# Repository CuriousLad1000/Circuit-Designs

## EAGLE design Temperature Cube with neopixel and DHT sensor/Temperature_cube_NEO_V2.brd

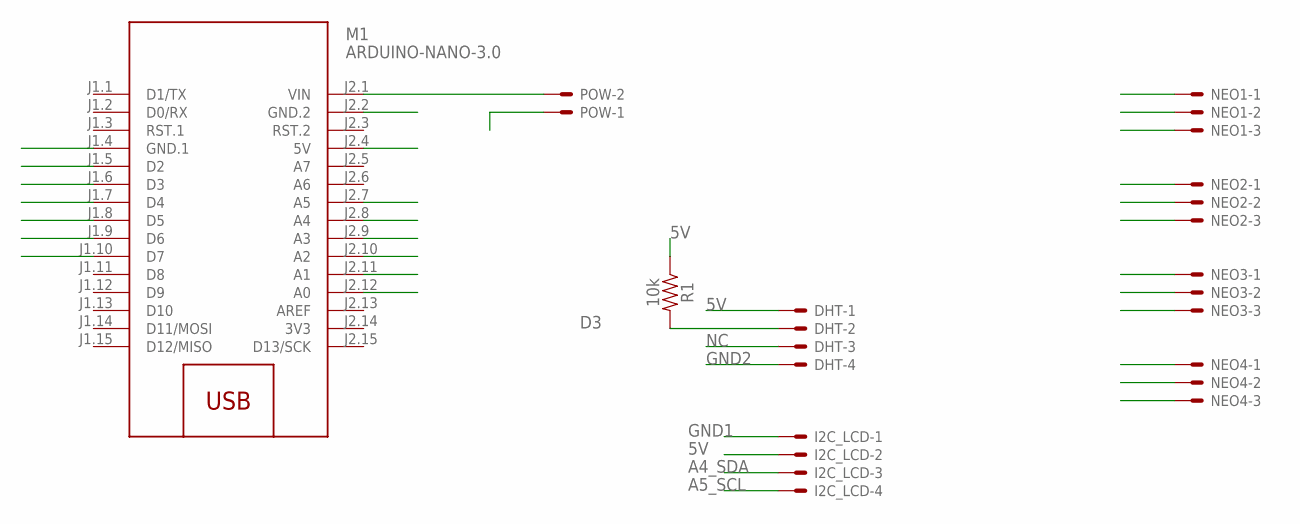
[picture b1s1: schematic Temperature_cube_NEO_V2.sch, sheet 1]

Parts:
DHT: JST-XH-04-PIN-ROUND-PAD; JST-XH-04-PACKAGE-ROUND-PAD
I2C_LCD: JST-XH-04-PIN-ROUND-PAD; JST-XH-04-PACKAGE-ROUND-PAD
M1: ARDUINO-NANO-3.0
NEO1, NEO2, NEO3, NEO4: JST-XH-03-PIN-ROUND-PAD; JST-XH-03-PACKAGE-ROUND-PAD
POW: JST-XH-02-PIN-ROUND-PAD; JST-XH-02-PACKAGE-ROUND-PAD
R1: 10k; AXIAL-0.3

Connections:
3V3: M1.J2.14 (3V3)
5V: DHT.1, I2C_LCD.2, M1.J2.4 (5V), NEO1.1, NEO2.1, NEO3.1, NEO4.1, R1.P$1 (1)
A0: M1.J2.12 (A0), NEO1.2
A1: M1.J2.11 (A1), NEO2.2
A2: M1.J2.10 (A2), NEO3.2
A3: M1.J2.9 (A3), NEO4.2
A4_SDA: I2C_LCD.3, M1.J2.8 (A4)
A5_SCL: I2C_LCD.4, M1.J2.7 (A5)
D2: M1.J1.5 (D2)
D3: DHT.2, M1.J1.6 (D3), R1.P$2 (2)
D4: M1.J1.7 (D4)
D5: M1.J1.8 (D5)
D6: M1.J1.9 (D6)
D7: M1.J1.10 (D7)
GND1: I2C_LCD.1, M1.J1.4 (GND.1), NEO3.3, NEO4.3
GND2: DHT.4, M1.J2.2 (GND.2), NEO1.3, NEO2.3, POW.1
NC: DHT.3
POW: M1.J2.1 (VIN), POW.2

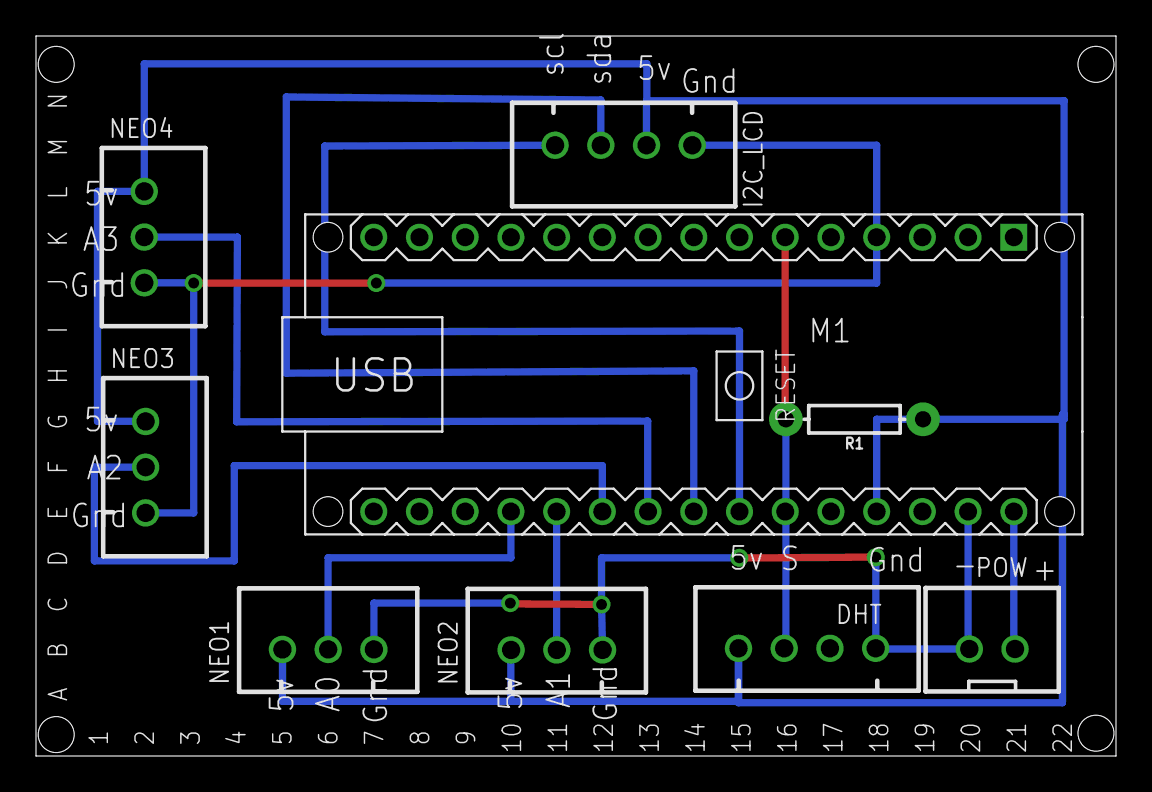
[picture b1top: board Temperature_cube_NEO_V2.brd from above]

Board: 2 copper layers, 60.0 x 40.0 mm, 31 parts (0 on the bottom side), 11 nets.

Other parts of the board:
U$1, U$2, U$3, U$4, U$5, U$6, U$7, U$8, U$9, U$10, U$11, U$12, U$13, U$14, U$15, U$16, U$17, U$18, U$19, U$20, U$21, U$22: 1X14

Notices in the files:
parts and their libraries:
SparkFun-Resistors: Licensing: Creative Commons ShareAlike 4.0 International - https://creativecommons.org/licenses/by-sa/4.0
diy-modules: Released under the Creative Commons Attribution 4.0 International License: http://creativecommons.org/licenses/by/4.0
